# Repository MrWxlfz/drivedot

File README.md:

# DriveDot

*revision a CAD render — this hasn't been printed or built yet!!!!1*

a little dashboard gadget that tells you how smooth your driving is.

drivedot is an ESP32-S3 with an IMU and a tiny OLED. it reads acceleration, braking, and cornering, draws a live g-force dot on the screen, and gives you a summary when the drive ends. runs off usb, doesn't touch the car's electronics at all.

i'm learning to drive, so i wanted my first hardware project to be something i'd actually use. it's my warm-up project for hack club half-life.

## where it's at

revision a has an actual schematic, routed carrier pcb, printable case and firmware. i used ai to help create these files. the source, exports and checks are here so i can review them, make changes and build the prototype.

- **designed:** 60 × 40 mm, two-layer carrier pcb with XIAO sockets, screen/sensor headers and a button
- **modeled:** screw-fastened case, screen clamp, flat sensor cradle and button plunger
- **implemented:** standalone button controls, calibration, live display, session summary and usb csv
- **checked:** schematic/pcb rules and portable motion, button and calibration tests; see [validation](docs/validation.md)
- **still to do:** measure the real modules, confirm the full cost, print, solder, bench-test and record the results
- **planned:** a small ws2812 rgb led strip that goes green → yellow → red as the forces get harsher. it isn't on the revision a pcb or in the case cad yet, so it's not in the parts list

no physical fit test or road test yet, so no accuracy claims from me. the half life parts list is at about $63.99 for tier 2 ($65): digikey and amazon parts, pcbs from jlcpcb, the seven-part enclosure printed by jlc3dp in 9600 resin, screws from bolt depot, plus shipping, tariffs and a tax ceiling. bolt depot's shipping and soldering supplies aren't in that total, and tax and the final pcb order total are estimates until checkout. 9600 resin softens at about 56 °c, so the first print is a fit test only and not something to leave on a hot dash. nothing has been ordered yet. the parts research and pricing were done with claude.

## open the design

| what | files |
| --- | --- |
| schematic, routed board and fabrication exports | [KiCad project](hardware/pcb/README.md) |
| printable parts, editable CAD, STEP and renders | [enclosure](hardware/enclosure/README.md) |
| parts and required quantities | [selected parts](hardware/parts.md) · [planning BOM](hardware/bom.csv) |
| putting it together | [assembly guide](docs/assembly.md) · [wiring](hardware/wiring.md) |
| firmware and controls | [firmware setup](docs/firmware.md) |
| what's checked and what still needs testing | [validation](docs/validation.md) · [build plan](docs/build-plan.md) |

*exploded CAD view. the screen and sensor connect with short wires; their modeled envelopes still need checking against the received parts.*

## version 1

- Seeed Studio XIAO ESP32S3, GY-521 MPU6050 and 128 × 64 SSD1306 OLED
- hold the button for 1.5 seconds, then release to calibrate while parked and still
- short press/release to start or end a session
- live forward/lateral acceleration and a g-force dot
- summary with peak g and sustained-event counts
- csv over usb serial for checking the numbers

the score is a rough smoothness thing, not a safety grade. hills, bumps, sensor drift, and a shifted mounting angle all mess it up. check the summary while parked. the live feedback is really for a passenger during testing. mount it solid, flat, out of your line of sight and away from airbags.

## running it

1. read the [assembly guide](docs/assembly.md), [schematic notes](docs/first-schematic.md) and [wiring](hardware/wiring.md).
2. open `firmware/` in VS Code with PlatformIO. the selected board is `seeed_xiao_esp32s3`.
3. build and upload through the XIAO's USB-C port with a data cable:

```sh
cd firmware
pio run
pio run --target upload
pio device monitor
```

4. mount the sensor flat and keep it still. hold the button for 1.5 seconds and release when prompted. after calibration, tap to start and tap again to end.
5. serial commands also work: `c` calibrates, `n` starts and `e` ends. see [firmware setup](docs/firmware.md) for errors and limitations.

to run the logic tests without a microcontroller:

```sh
python3 scripts/test.py
```

## license

MIT. see [LICENSE](LICENSE).

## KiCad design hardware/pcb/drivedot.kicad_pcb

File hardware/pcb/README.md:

# DriveDot carrier — revision A

This is an actual two-layer KiCad design with a routed PCB, schematic, Gerbers and drill files. It is **an unbuilt prototype design**. Electrical and design-rule checks pass; received-part fit, assembly, power-up and driving measurements have not been tested.

## Open the design

Open [`drivedot.kicad_pro`](drivedot.kicad_pro) in **KiCad 9**. The project-local symbols, footprints and library tables are included. There are no library downloads needed to edit this board.

- [Schematic PDF](exports/drivedot-schematic.pdf) · [schematic image](exports/drivedot-schematic.png)
- [Front copper preview](exports/drivedot-front.png) · [back copper preview, mirrored](exports/drivedot-back.png)
- [Schematic source](drivedot.kicad_sch) · [PCB source](drivedot.kicad_pcb)
- [Fabrication exports](fabrication/) · [fabrication ZIP](drivedot-rev-a-gerbers.zip)
- [ERC report](validation/erc.rpt) · [DRC and schematic-parity report](validation/drc.rpt)
- [Footprint evidence and license](SOURCES.md)

## Circuit and assembly

U1 holds the **standard Seeed XIAO ESP32S3**, USB facing the `USB` silkscreen. Solder two 1×7, 2.54 mm male headers to the XIAO and matching female sockets to the carrier. The 15.24 mm spacing between socket rows follows Seeed's official footprint. Socket mounting avoids pressing the XIAO's underside components against this carrier.

The display and GY-521 are mounted separately in the enclosure and joined with short insulated wires. J1 and J2 are **different power orders**. Their pin 1 pads are square. Viewed from the component side, pins increase left to right:

| Carrier pin | J1 → OLED | J2 → GY-521 |
| --- | --- | --- |
| 1 | GND | VCC / 3.3 V |
| 2 | VCC / 3.3 V | GND |
| 3 | SCL | SCL |
| 4 | SDA | SDA |

Connect the other end by the module's printed labels, including when a supplied header orientation differs. U1 D4/GPIO5 supplies SDA, D5/GPIO6 supplies SCL, and D3/GPIO4 reads SW1. Leave the sensor's AD0 low for address `0x68`; the OLED is expected at `0x3C`. The 5 V XIAO header pad is intentionally unconnected.

SW1 is a 6 mm tactile switch with 6.5 × 4.5 mm lead spacing. The two pads along each horizontal row are the same switch terminal. Confirm this with a continuity meter before soldering an alternate switch. Its actuator height must match the enclosure's adjustable button stem.

**R1 and R2 are optional 4.7 kΩ pull-ups and default to DNP (do not populate).** The footprints use 7.62 mm axial lead pitch. Selected modules may already contain pull-ups; adding another pair blindly changes the bus loading. Neither resistor is needed in the default carrier purchase list until the actual modules are inspected.

### Power-up checks

1. Unplug USB. Check socket orientation, continuity, absence of a 3.3 V-to-ground short, and all four harness wires against their labels.
2. Power the XIAO alone first, then connect the modules with USB unplugged. Power comes only from the XIAO USB-C port.
3. Measure the carrier 3.3 V rail and the GY-521's actual regulated sensor rail. The supplier lists 3.3 V VCC operation, but generic GY-521 regulator revisions vary. A dropout-prone module can undervolt the sensor; verify its rail against the actual regulator and MPU6050 specifications.
4. Check idle SDA/SCL voltages and the modules' pull-up supply rails. All bus signals must be compatible with the XIAO's 3.3 V logic. If the breakout revision is incompatible, change the module or design before using it; do not move J2 to 5 V by improvising a wire.
5. Run an I2C scanner, verify `0x68` and `0x3C`, then verify sensor axis directions and the button before closing the case.

Mount the IMU flat and rigidly: X forward, Y left, Z up. Calibration and vehicle motion testing still need to be done. This carrier has no connection to vehicle control or wiring.

## Mechanical interface

Coordinates are millimetres, viewed from above, origin at the carrier's USB-side left corner. Positive X runs right; positive Y runs away from the USB edge.

| Feature | Position / dimensions |
| --- | --- |
| Carrier | 60 × 40 × 1.6 mm |
| Non-plated mounting holes | Ø3.2 mm at (4,4), (56,4), (56,36), (4,36) |
| XIAO centre | (17,11), USB toward negative Y |
| XIAO board envelope | X 8.1–25.9; Y 0.5–21.5 mm |
| XIAO pin rows | X 9.38 / 24.62; first row Y 3.38; 2.54 mm pitch |
| J1 OLED | Pin 1 at (43,7); four pads along +X, 2.54 mm pitch |
| J2 IMU | Pin 1 at (43,20); four pads along +X, 2.54 mm pitch |
| SW1 actuator centre | (17,30) |
| R1 / R2 | Pin 1 at (30,27) / (30,33), 7.62 mm pitch along +X |

Allow up to **16 mm above the carrier** for an ordinary socket, male header, XIAO board and USB connector stack. This is a clearance allowance, not a measured supplied-part height. Check the actual header stack and cable moulding before printing a final enclosure. The USB shell extends approximately 1 mm beyond the carrier's Y=0 edge. The XIAO uses an external U.FL antenna connector; this firmware does not enable radio functions. There is no fictional on-board antenna keepout. If radio functionality is added, the external antenna must be placed and verified separately.

## Fabrication and validation

Suggested prototype fabrication settings: **two-layer FR-4, 1.6 mm, 1 oz copper**, ordinary solder mask, plated component holes and separate non-plated mounting holes. Board dimensions and hole type must be checked in the fabricator's viewer before ordering. The ZIP contains manufacturing files; it is not evidence of assembly or electrical operation.

KiCad **9.0.9** reports **0 ERC violations, 0 DRC violations, 0 unconnected items and 0 schematic-parity issues**, with warnings and exclusions included. No ERC or DRC issues are excluded. The four mechanical holes are intentionally board-only footprints. Tracks are 0.25 mm with a 0.20 mm minimum clearance. There are 30 plated component holes and 4 non-plated mounting holes; this layout needs no vias.

The generator and exports are reproducible:

```bash
/usr/bin/python3 scripts/generate_pcb.py
bash scripts/generate_pcb_exports.sh
```

Run from the repository root with KiCad 9's Python `pcbnew` module and CLI installed. The generator rebuilds sources and can overwrite manual CAD edits. Editing the committed KiCad files directly is also supported; rerun the export script after editing. It removes the previous fabrication ZIP before checking the design, and recreates the ZIP and validation hashes only after checks pass. Install the optional `cairosvg` Python package to refresh PNG previews in the same command; native SVG/PDF exports do not need it. PNG previews are rasterizations of the native SVG exports, not concept artwork. The supplied component and net names are checked against an exported schematic netlist before routing, and KiCad independently checks schematic/PCB parity afterward.

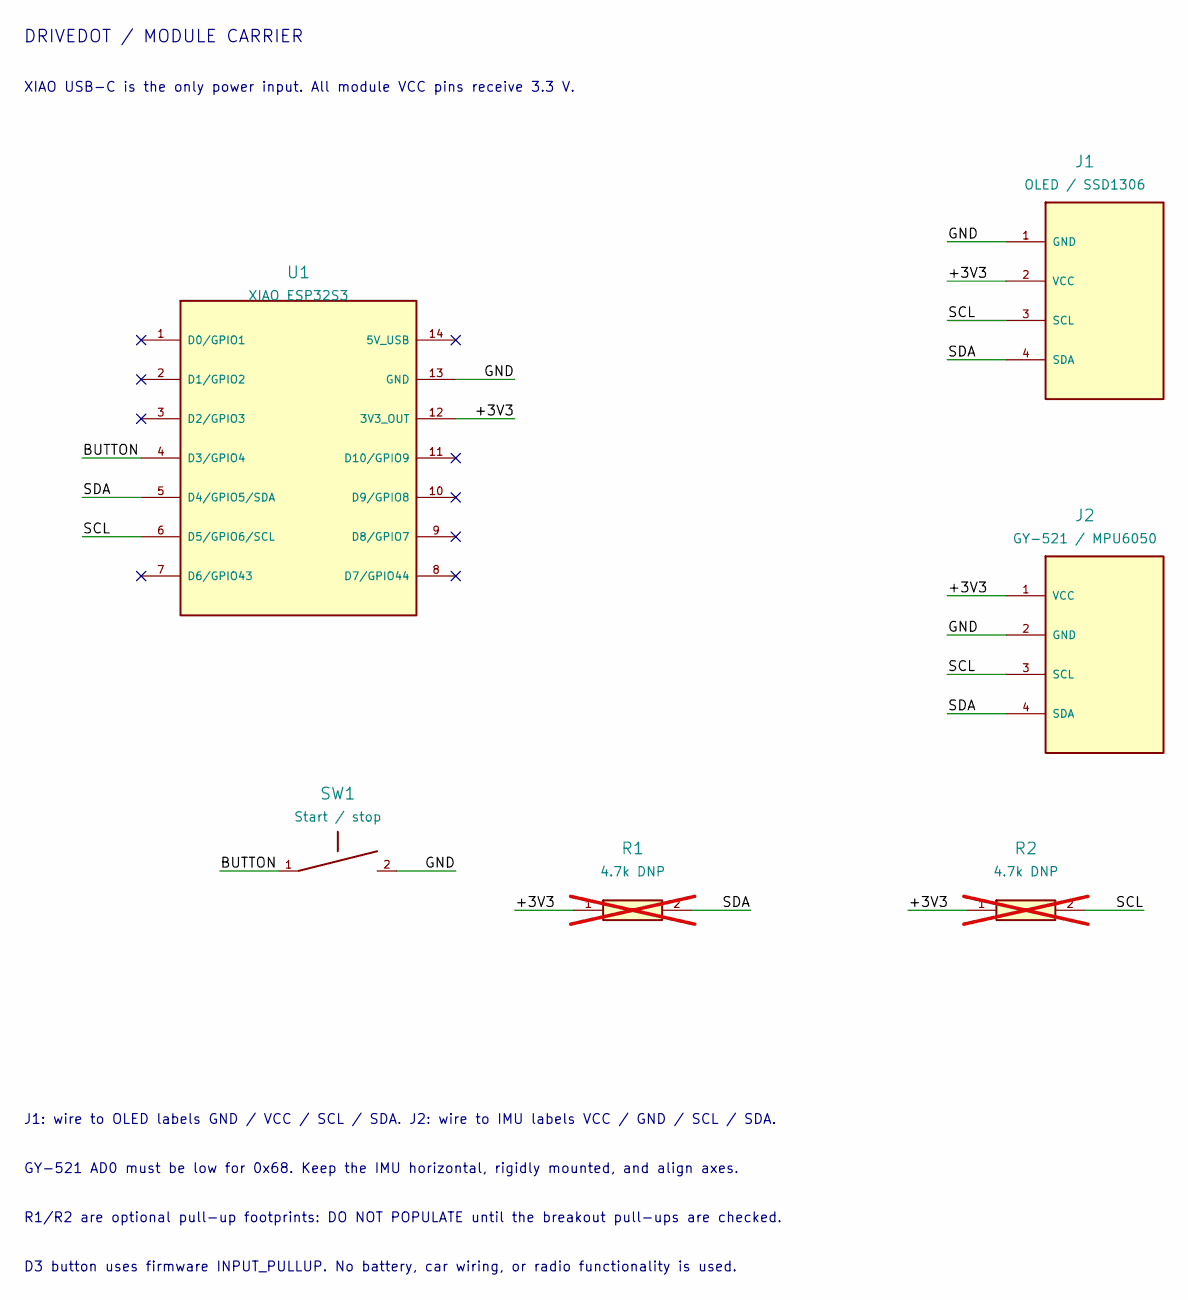
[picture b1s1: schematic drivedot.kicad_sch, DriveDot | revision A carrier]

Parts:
J1: OLED / SSD1306; Header_1x04
J2: GY-521 / MPU6050; Header_1x04
R1, R2: 4.7k DNP; R_Axial_P7.62; not fitted
SW1: Start / stop; Tactile_6mm
U1: XIAO ESP32S3; XIAO_Socket

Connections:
/+3V3: J1.2 (VCC), J2.1 (VCC), R1.1, R2.1, U1.12 (3V3_OUT)
/BUTTON: SW1.1, U1.4 (D3/GPIO4)
/GND: J1.1 (GND), J2.2 (GND), SW1.2, U1.13 (GND)
/SCL: J1.3 (SCL), J2.3 (SCL), R2.2, U1.6 (D5/GPIO6/SCL)
/SDA: J1.4 (SDA), J2.4 (SDA), R1.2, U1.5 (D4/GPIO5/SDA)

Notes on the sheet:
DRIVEDOT / MODULE CARRIER
XIAO USB-C is the only power input. All module VCC pins receive 3.3 V.
J1: wire to OLED labels GND / VCC / SCL / SDA. J2: wire to IMU labels VCC / GND / SCL / SDA.
GY-521 AD0 must be low for 0x68. Keep the IMU horizontal, rigidly mounted, and align axes.
R1/R2 are optional pull-up footprints: DO NOT POPULATE until the breakout pull-ups are checked.
D3 button uses firmware INPUT_PULLUP. No battery, car wiring, or radio functionality is used.

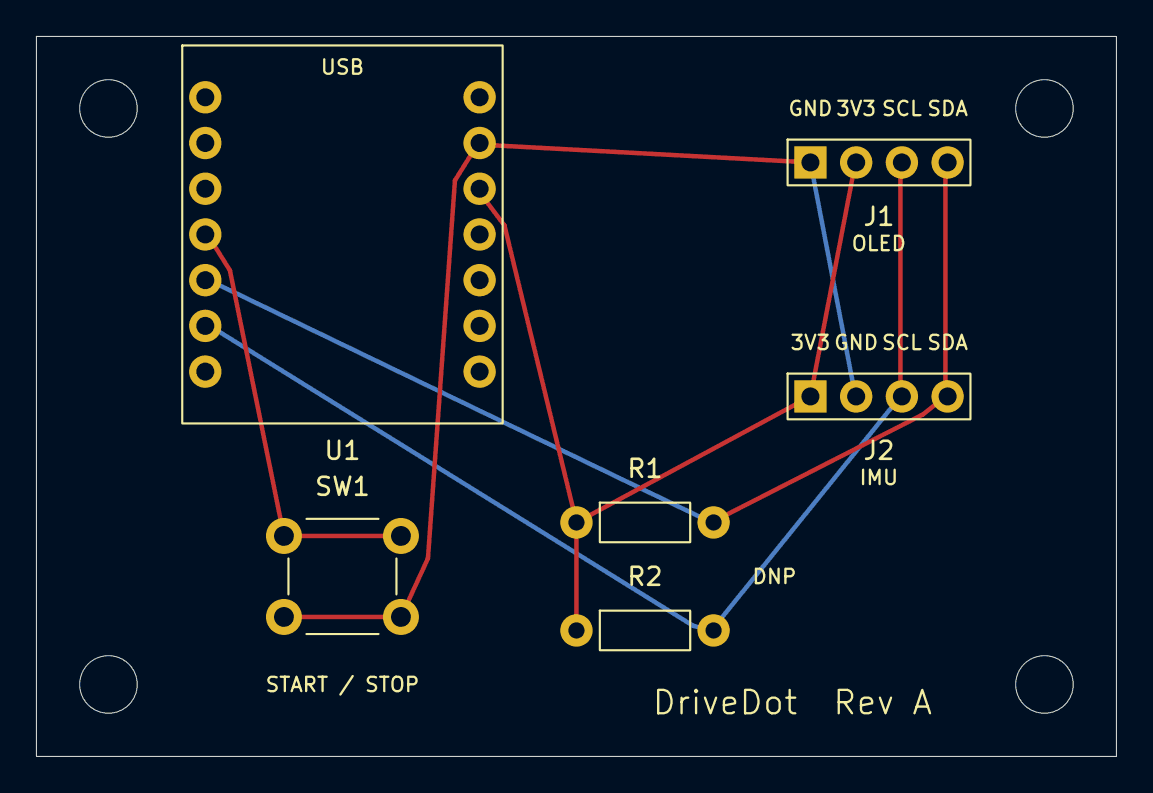
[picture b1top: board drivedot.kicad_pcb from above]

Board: 2 copper layers, 60.0 x 40.0 mm, 10 parts (0 on the bottom side), 5 nets.

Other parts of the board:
H1, H2, H3, H4: M3; MountingHole_M3
